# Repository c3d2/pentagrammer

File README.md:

pentagrammer
============

A darn cheap AVR ISP Programmer with TTH only components

If you plug it in, it get's recognized as a USBtiny.

Installation Windows
===========

After you plugged in the programmer, check if you can find it in
your device manager. There should be a "USBtiny" device somewhere.
You can find all necessary drivers at adafruit.com:
	
	https://learn.adafruit.com/usbtinyisp/avrdude

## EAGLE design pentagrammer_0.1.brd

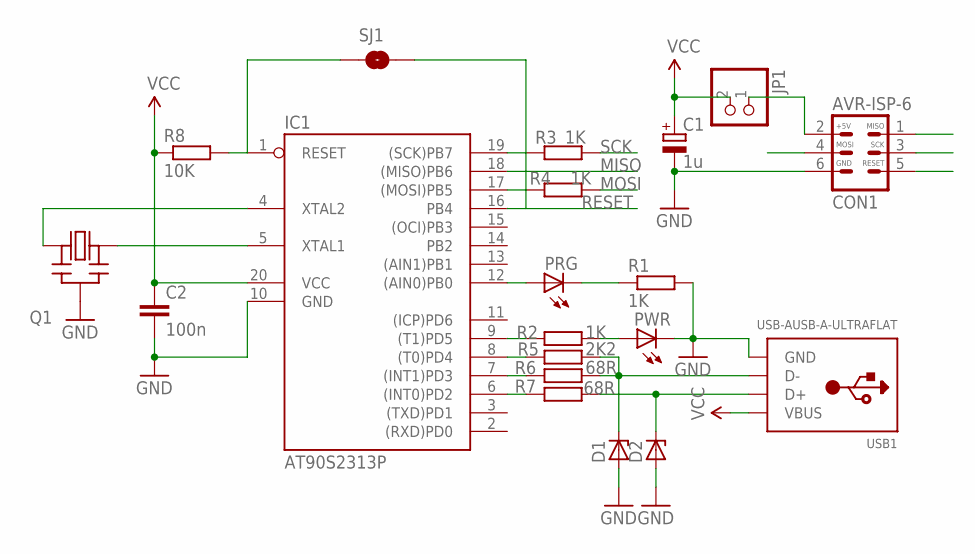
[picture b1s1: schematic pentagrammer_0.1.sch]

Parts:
C1: 1u; E1,8-4
C2: 100n; C025-024X044
CON1: AVR-ISP-6; ML6
D1, D2: ZENER-DIODEZD-5; ZDIO-5
IC1: AT90S2313P; DIL20
JP1: PINHD-1X2; 1X02
PRG: LED3MM
PWR: LED3MM
Q1: CERMOSCILL-THM; CERM_OSC
R1, R2, R3, R4: 1K; 0204/7
R5: 2K2; 0204/7
R6, R7: 68R; 0204/7
R8: 10K; 0204/7
SJ1: SOLDERJUMPERNO; SJ_2S-NO
USB1: USB-AUSB-A-ULTRAFLAT; USB-A-H

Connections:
GND: C1.-, C2.2, CON1.6 (GND), D1.A, D2.A, IC1.10 (GND), PWR.K (C), Q1.P$2 (GND), R1.2, USB1.GND, USB1.GND2 (GND), USB1.GND3 (GND)
MISO: CON1.1 (MISO), IC1.18 ((MISO)PB6)
MOSI: CON1.4 (MOSI), R4.2
unnamed: CON1.2 (+5V), JP1.1
unnamed: IC1.19 ((SCK)PB7), R3.1
unnamed: IC1.4 (XTAL2), Q1.P$1 (IN)
unnamed: IC1.5 (XTAL1), Q1.P$3 (OUT)
unnamed: IC1.9 ((T1)PD5), R2.1
unnamed: IC1.12 ((AIN0)PB0), PRG.A
unnamed: IC1.8 ((T0)PD4), R5.1
unnamed: IC1.7 ((INT1)PD3), R6.1
unnamed: IC1.6 ((INT0)PD2), R7.1
unnamed: D1.C, R5.2, R6.2, USB1.D-
unnamed: D2.C, R7.2, USB1.D+
unnamed: IC1.17 ((MOSI)PB5), R4.1
unnamed: IC1.1 (RESET), R8.2, SJ1.1
unnamed: PWR.A, R2.2
unnamed: PRG.K (C), R1.1
RESET: CON1.5 (RESET), IC1.16 (PB4), SJ1.2
SCK: CON1.3 (SCK), R3.2
VCC: C1.+, C2.1, IC1.20 (VCC), JP1.2, R8.1, USB1.VBUS

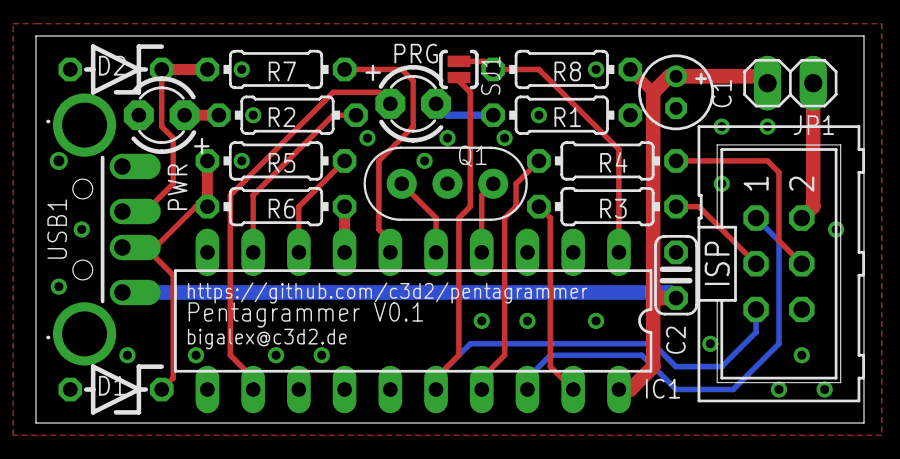
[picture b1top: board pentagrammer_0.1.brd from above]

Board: 2 copper layers, 46.0 x 21.5 mm, 20 parts (0 on the bottom side), 21 nets.

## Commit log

2014-11-30 first pcb layout for v.01
2015-01-04 added values for resistors
2015-03-20 added some installation notes for windows

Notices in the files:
parts and their libraries:
SparkFun: Licensing: CC v3.0 Share-Alike You are welcome to use this library for commercial purposes.
